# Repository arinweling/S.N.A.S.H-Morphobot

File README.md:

<!-- DON'T MODIFY ANYTHING ABOVE -->

<!-- Modify from here -->
<!-- ### EDL 2025 Project Submission Repository.

Change this file to include the relevant information of your project. Refer to SUBMISSION_INSTRUCTIONS.md file and follow it for your final submission. Make sure to pass the GitHub Actions. (The Docs Added should turn green and it should say "passing") -->

https://github.com/user-attachments/assets/5dc95bf6-1b18-49de-8811-edd3fce2244d

# S.N.A.S.H. - Your Friendly Neighbourhood MorphoBot
## MON-10
## Team Members:
- Sthiti Padhi
- Neel Bhavesh Rambhia
- Arin Prashant Weling
- Saumya Dharmesh Shah
- Harshil Singla

## Problem Statement and Solution:
### Problem Statement
Robots designed exclusively for ground travel or aerial operation often encounter significant challenges when faced with unpredictable or mixed environments. Ground-based robots may be unable to overcome obstacles or reach elevated areas, while aerial robots are limited by battery constraints and inefficiency during extended ground operations.

The problem is to create a robotic platform that can seamlessly transition between driving and flying, allowing it to navigate a wide range of terrains and obstacles efficiently. The system should provide the user with the ability to switch modes as needed to maximize energy efficiency and reach locations that would be inaccessible to single-mode robots.

### Solution
We developed **S.N.A.S.H.**, a multi-modal robotic system capable of:

- **Driving**: Increasing battery life and locomotive abilities for ground traversal.
- **Flying**: Quadcopter mode helps navigate over obstacles or difficult terrain.
- **Morphing**: A custom servo setup to switch between drive and drone configurations.

The system is controlled by a single flight controller that dynamically switches outputs to:
- 1 motor driver (controlling two motors via IN1 and two motors via IN2) (drive mode)  
- 4-in-1 ESC on SpeedyBee (flight mode)
- 4 Servo motors from their dedicated PCBs
based on mode-switch commands from the user through the RC transmitter.

### Folder Structure:
```plaintext
/Project-Root
├── /others
    ├── future_work.md/
    ├── learnings_takeaways.md/
    ├── user_manual.md/
    ├── README.md/
 
├── /3d_models               # laser cuts and 3d prints
    ├── Chassis/
    ├── Wheel_Assembly/
    ├── README.md/          
 
├── /pcb                    # pcb design files
    ├── PCB1/
    ├── Resources/
    ├── README.md/

├── /milestone reports

├── /inav

├── /Ardupilot                    # source folder
    ├── ArduCopter/         # we used ArduCopter and added files here
        ├── Copter.cpp
        ├── mode.cpp
        ├── mode_drive.cpp
        ├── mode_morph.cpp
        ├── mode_stabilize.cpp
        ├── README.md/      # describes the changes made, marked as 'EDL-MON10'
        └── ...
    
    ├── ArduPlane/  
    
    ├── ArduRover/
    
    ├── libraries/          # modified hwdef for gpio, default params
        ├── AP_HAL/
        ├── AP_HAL_ChibiOS/
        ├── AP_Motors/      # To use extra motor output or change motor functions - to be done here
        └── ...
    
    ├── modules/            
    
    ├── Tools/              # Developer tools, test scripts, MAVProxy, etc.
    
    ├── build/              # Build scripts and configuration
    
    ├── docs/               # Documentation
    
    ├── wscript             # Waf build system entry point
    └── README.md           # Project overview and setup instructions

```

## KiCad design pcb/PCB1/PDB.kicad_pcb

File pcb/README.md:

## Description

The PCB has two Buck regulator IC's (LMR14050) that step down the voltage from 14.8V-16.8V (4S LiPo Battery) to 7.4V in order to power the Servo Motors. Since there are 4 servo motors, two PCB's (and thus 4 IC's) are used for the same. The circuit is simply designed from the datasheet specifications given. 

The PCB was designed on KiCad 8.0 and maufactured from PCB Power (external vendor) since via size on IC footprint was quite small.

## How to use this directory

Download or clone this repository to get all the necessary files. Edit the "fp-lib-table" and "sym-lib-table" files to include _your_ path for the symbols and footprints required. All symbol and footprint files are within the "Resources" directory.

## Quick Verification of the PCB after Manufacturing

Testpoints are provided on the PCB for quick verification of the output voltage. LED's are also present and can be used as a visual indicator but not necessarily reliable (a range of voltage will turn it on, you can't assume it is 7.4V only). Also, the LED is optional and may be removed or not soldered and the PCB would work fine.

## Calculations for the circuit

#### LMR14050 Buck Switching Regulator IC  

Input Voltage - 14.8V 

Output Voltage - 7.4V 

Max Output Current - 3.8A 

Transient Response - 5% 

Soft-Start time - 5ms 

#### Output Voltage Setpoint: 

R_FBT = (14.8-0.75)/0.75 * R_FBB 

So, R_FBT = 160k & R_FBB = 18k 

#### Output Inductor Selection: 

L=4.7uH (available from WEL) 

Lmin =  [(14.8-7.4)/(3.8*0.4)] * [7.4/(14.8*f)] = 2.4342 / f 

For Lmin = 4.7uH => f = 517kHz 

Take Switching Frequency 750kHz => Lmin = 3.24uH 

#### Switching Frequency: 

f = 750kHz 

R_T = 32.4k 

Closest available R_T = 33k => f=732kHz 

#### Output Capacitor: 
100uF (25V) x2 in Parallel 

#### Schottky Diode: 
5-6A rated Schottky diode 

<https://www.googleadservices.com/pagead/aclk?sa=L&ai=DChcSEwi1pe33-riLAxV_p2YCHWZMDQwYABADGgJzbQ&ae=2&aspm=1&co=1&ase=5&gclid=CjwKCAiA5Ka9BhB5EiwA1ZVtvMta-bck2QZtikhFSwPQNB7W7tcWDABVQjyAaNMlUeXBK18xhEKkKRoCkBsQAvD_BwE&ohost=www.google.com&cid=CAESVeD2yFSM_nJpq_IPCykuUYeB5w_LyxcPm_9DhT0_zzm2AJfOdDbZZ1pPT8ZjT5nLCw1axiebZy9D2vHVyNDqCvjmDnesfMkeMb1UFT9ZSRDTL9Qf3vY&sig=AOD64_19A6xZXjguXm5rXCT6MYhL_5oAdA&ctype=5&q=&ved=2ahUKEwjA1Of3-riLAxWlRWwGHe09F8AQ9aACKAB6BAgCEA8&adurl=>

#### Input capacitor: 
10uF (35V) + 0.1uF for high frequency filtering 

#### Bootstrap: 
0.1uF (16V) 

## Testing Plan

1. Solder only one IC and test it before soldering the other one 
2. Use DC Power Supply and give 14.8V input voltage in CV mode by attaching to XT60 using alligator clips 
3. Attach a high resistance (10kOhm) to output and turn on the power supply (LED should light up) 
4. Check VIN and GND test points to confirm 14.8V and 0V 
5. Check VOUT test point to confirm 7.4V 
6. Decrease resistance to check performance when higher current is drawn 
7. Decrease resistance till 2.2 Ohm (use power resistor since current capacity is exceeded at such low resistance 
8. Apply a PWM signal to center jumper (J4) and check the signal using oscilloscope on Pin1 of J2 and J3 
9. Remove power supply and attach 4S LiPo battery. Check the output voltage again and performance with 2.2Ohm again 
10. Remove resistor and attach servo motor. Give a PWM using any simple microcontroller and check correct functioning. 
11. Attach the servo arm and apply heavy load to make the servo motor stall. Check that IC is working properly even when stalling. 
12. Repeat for 2nd IC.

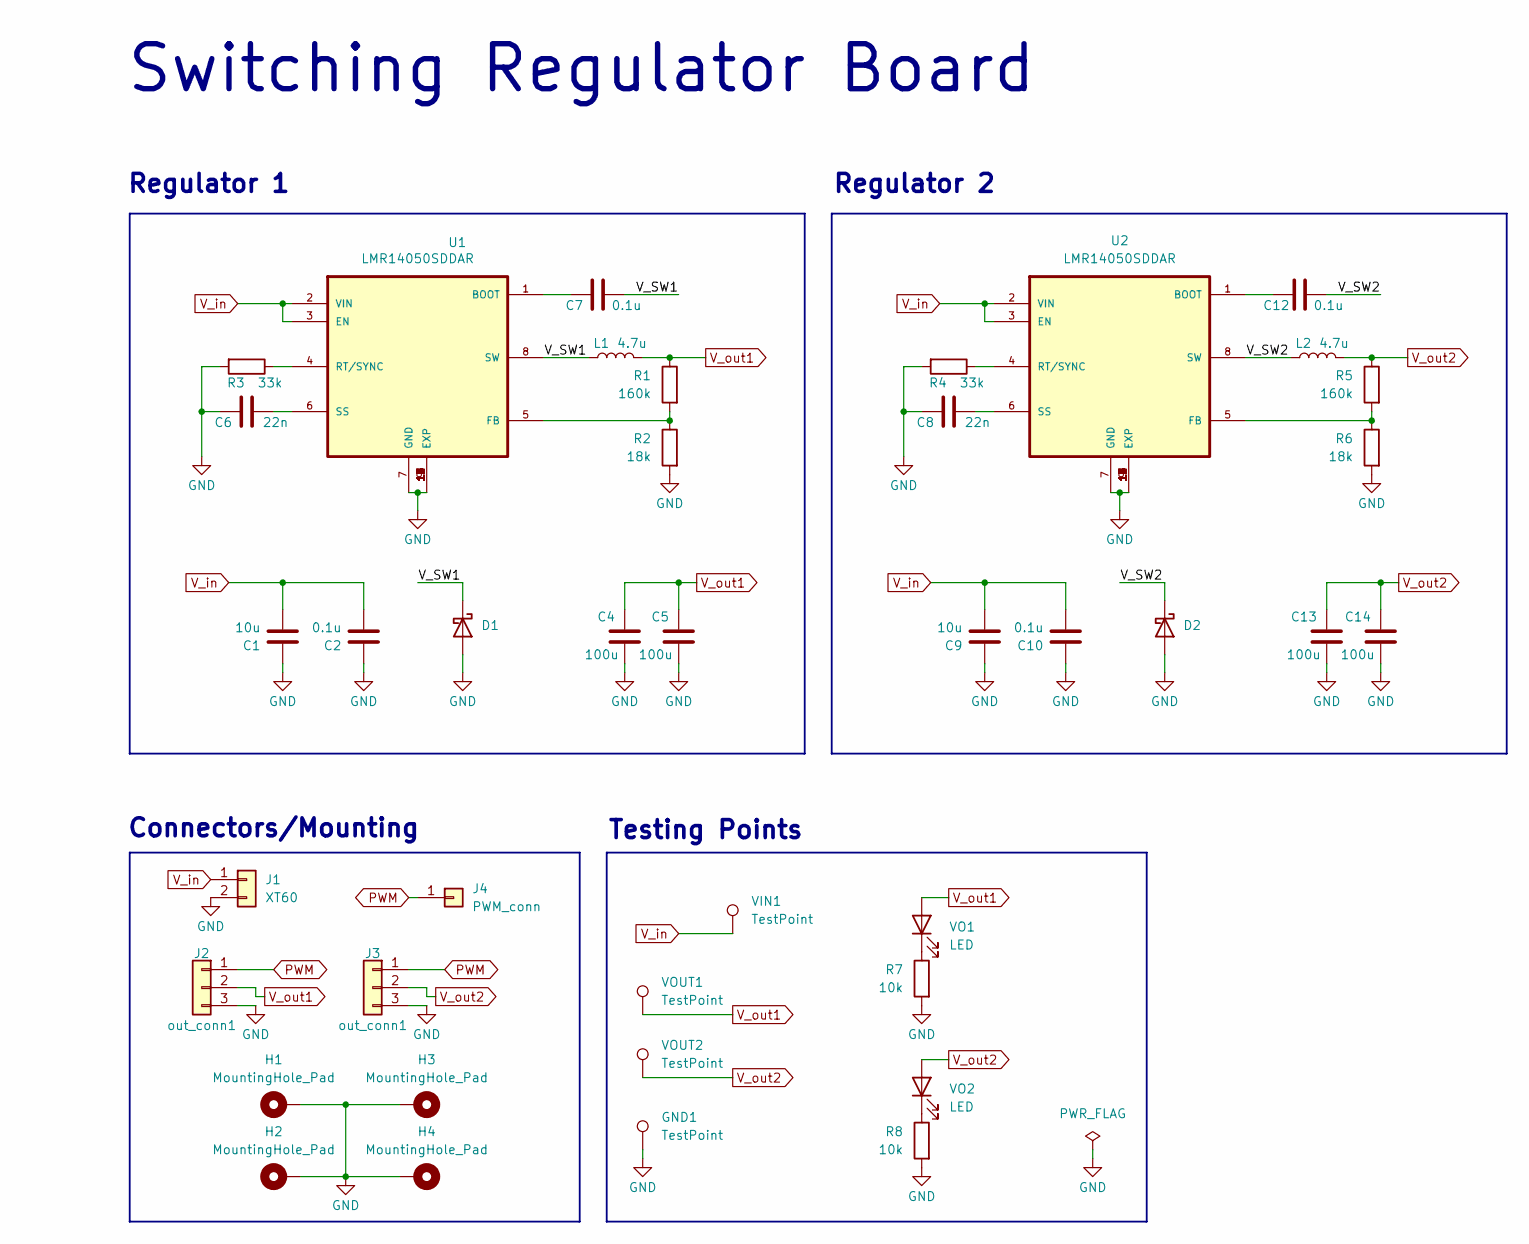
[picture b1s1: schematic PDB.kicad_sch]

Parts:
C1, C9: 10u; C_Radial_D5.0mm_H7.0mm_P2.00mm
C2, C7, C10, C12: 0.1u; C_0603_1608Metric_Pad1.08x0.95mm_HandSolder
C4, C5, C13, C14: 100u; C_Radial_D5.0mm_H7.0mm_P2.00mm
C6, C8: 22n; C_0603_1608Metric_Pad1.08x0.95mm_HandSolder
D1, D2: D_Schottky; SS54-Slkor
GND1: TestPoint; TestPoint_Pad_D1.0mm
H1, H2, H3, H4: MountingHole_Pad; MountingHole_2.2mm_M2_Pad_TopBottom
J1: XT60; AMASS_XT60-F_1x02_P7.20mm_Vertical
J2, J3: out_conn1; PinHeader_1x03_P2.54mm_Vertical
J4: PWM_conn; PinHeader_1x01_P2.54mm_Vertical
L1, L2: 4.7u; L_1210_3225Metric_Pad1.42x2.65mm_HandSolder
R1, R5: 160k; R_0805_2012Metric_Pad1.20x1.40mm_HandSolder
R2, R6: 18k; R_0805_2012Metric_Pad1.20x1.40mm_HandSolder
R3, R4: 33k; R_0805_2012Metric_Pad1.20x1.40mm_HandSolder
R7, R8: 10k; R_0805_2012Metric_Pad1.20x1.40mm_HandSolder
U1, U2: LMR14050SDDAR; VREG_LM5017MR_NOPB
VIN1: TestPoint; TestPoint_Pad_D1.0mm
VO1, VO2: LED; D_0805_2012Metric_Pad1.15x1.40mm_HandSolder
VOUT1, VOUT2: TestPoint; TestPoint_Pad_D1.0mm

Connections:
/V_SW1: C7.2, D1.1 (K), L1.1, U1.8 (SW)
/V_SW2: C12.2, D2.1 (K), L2.1, U2.8 (SW)
GND: C1.2, C2.2, C4.2, C5.2, C6.1, C8.1, C9.2, C10.2, C13.2, C14.2, D1.2 (A), D2.2 (A), GND1.1, H1.1, H2.1, H3.1, H4.1, J1.2, J2.3, J3.3, R2.2, R3.2, R4.2, R6.2, R7.2, R8.2, U1.7 (GND), U1.9 (EXP), U1.10 (EXP), U1.11 (EXP), U1.12 (EXP), U1.13 (EXP), U1.14 (EXP), U1.15 (EXP), U1.16 (EXP), U1.17 (EXP), U2.7 (GND), U2.9 (EXP), U2.10 (EXP), U2.11 (EXP), U2.12 (EXP), U2.13 (EXP), U2.14 (EXP), U2.15 (EXP), U2.16 (EXP), U2.17 (EXP)
unnamed: C7.1, U1.1 (BOOT)
unnamed: R1.2, R2.1, U1.5 (FB)
unnamed: R3.1, U1.4 (RT/SYNC)
unnamed: C6.2, U1.6 (SS)
unnamed: C12.1, U2.1 (BOOT)
unnamed: R5.2, R6.1, U2.5 (FB)
unnamed: R4.1, U2.4 (RT/SYNC)
unnamed: C8.2, U2.6 (SS)
unnamed: R7.1, VO1.1 (K)
unnamed: R8.1, VO2.1 (K)
PWM: J2.1, J3.1, J4.1
V_in: C1.1, C2.1, C9.1, C10.1, J1.1, U1.2 (VIN), U1.3 (EN), U2.2 (VIN), U2.3 (EN), VIN1.1
V_out1: C4.1, C5.1, J2.2, L1.2, R1.1, VO1.2 (A), VOUT1.1
V_out2: C13.1, C14.1, J3.2, L2.2, R5.1, VO2.2 (A), VOUT2.1

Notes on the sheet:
Testing Points
Connectors/Mounting
Switching Regulator Board
Regulator 1
Regulator 2

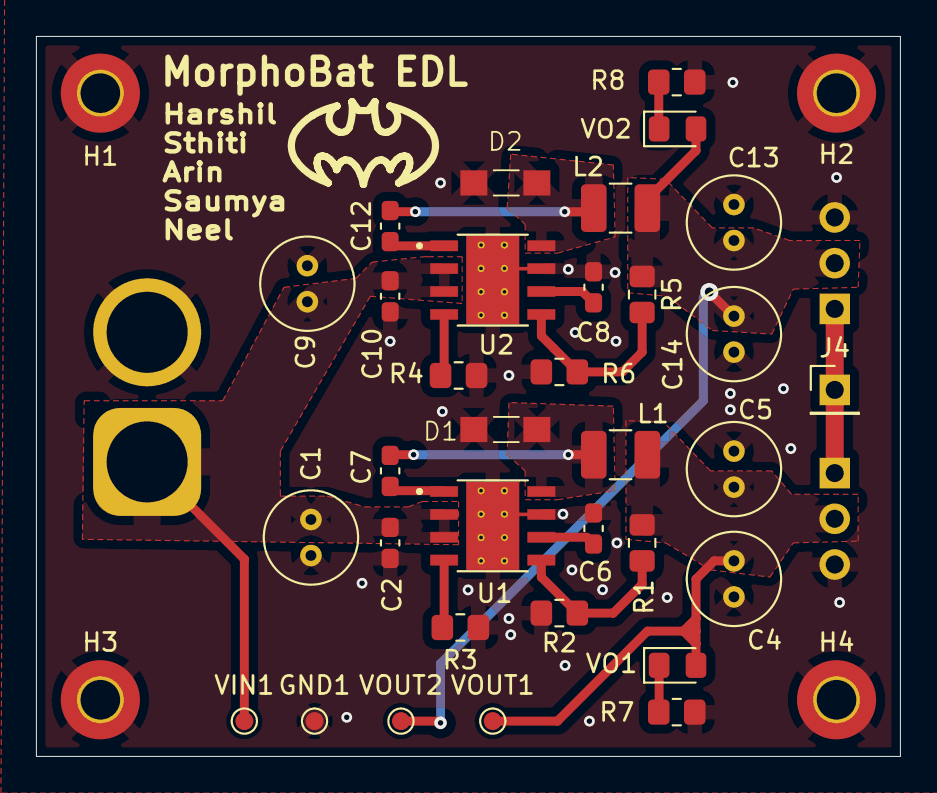
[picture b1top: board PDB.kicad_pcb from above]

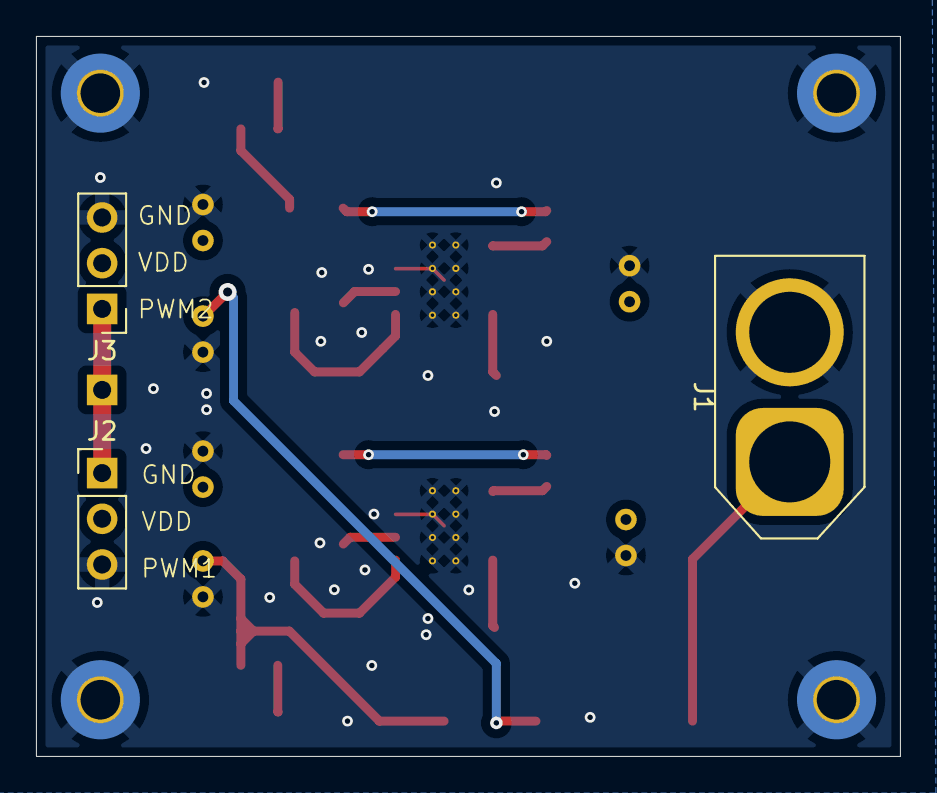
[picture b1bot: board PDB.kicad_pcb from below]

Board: 2 copper layers, 48.0 x 40.0 mm, 40 parts (3 on the bottom side), 17 nets.
